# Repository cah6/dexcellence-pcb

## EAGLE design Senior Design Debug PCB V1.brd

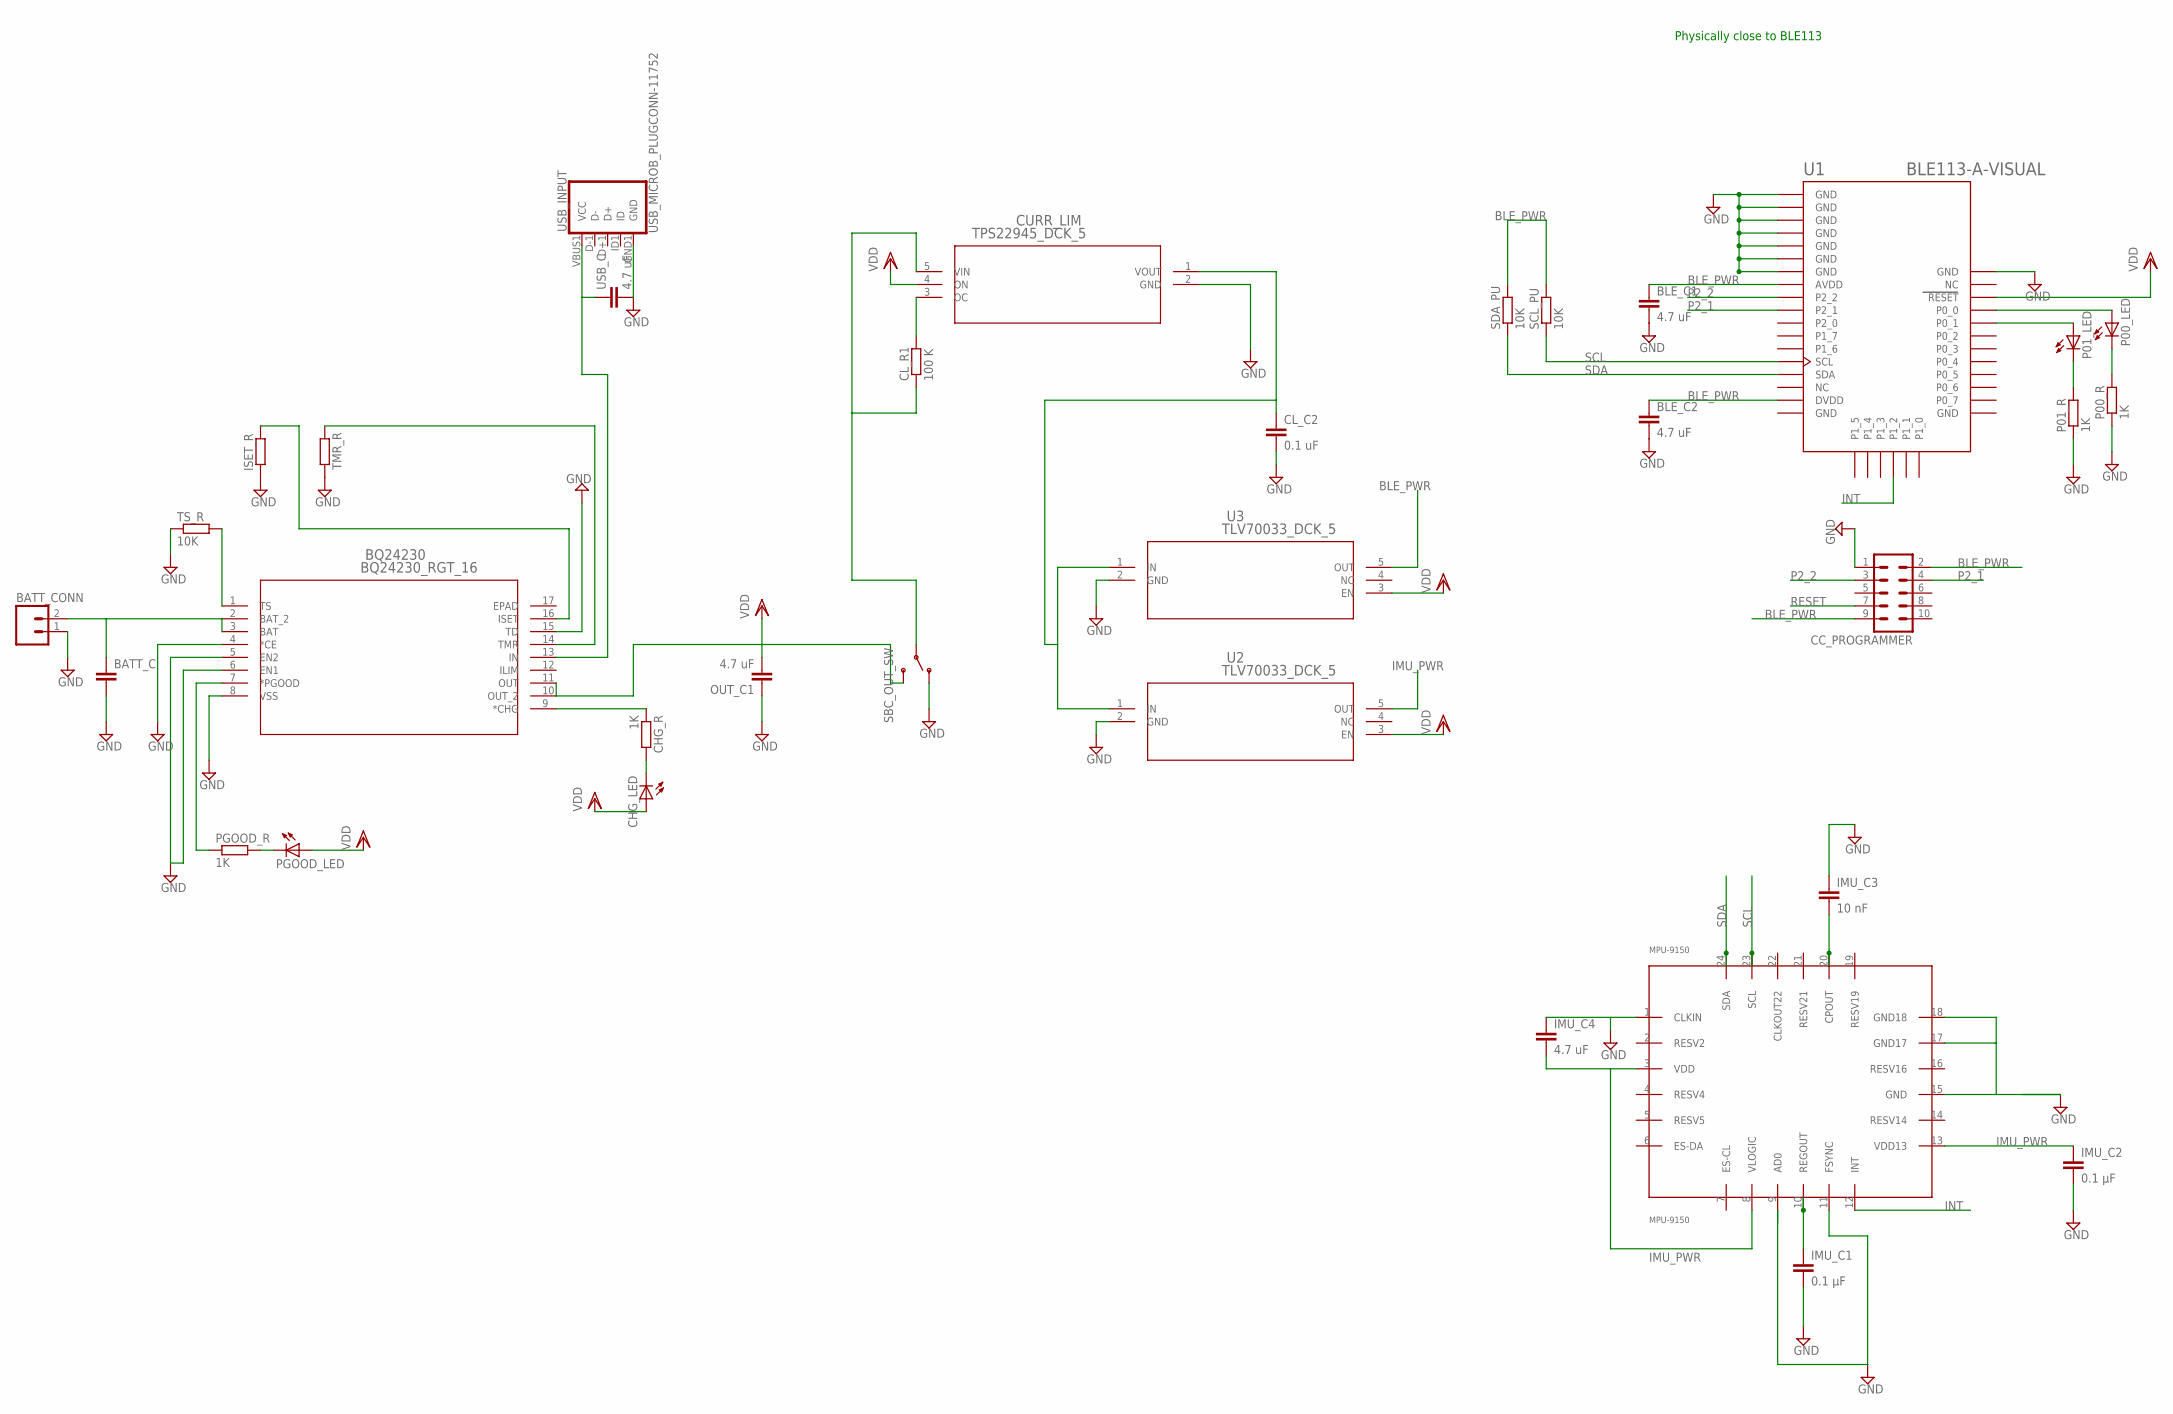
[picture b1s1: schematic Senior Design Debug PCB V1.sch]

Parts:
BATT_C: C; C0805
BATT_CONN: M02; 02P
BLE_C1, BLE_C2: 4.7 uF; C0805
BQ24230: BQ24230_RGT_16; RGT16_1P7X1P7
CC_PROGRAMMER: MA05-2
CHG_LED: LED_E; LED_1206
CHG_R: 1K; R0805
CL_C2: 0.1 uF; C0805
CL_R1: 100 K; R0805
CURR_LIM: TPS22945_DCK_5; DCK5
IMU_C1, IMU_C2: 0.1 µF; C0805
IMU_C3: 10 nF; C0805
IMU_C4: 4.7 uF; C0805
ISET_R: R; R0805
MPU-9150: MPU-9150
OUT_C1: 4.7 uF; C0805
P00_LED, P01_LED: LED_E; LED_1206
P00_R, P01_R: 1K; R0805
PGOOD_LED: LED_E; LED_1206
PGOOD_R: 1K; R0805
SBC_OUT_SW: SWITCH-SPDTPTH; SWITCH-SPDT
SCL_PU: 10K; R0805
SDA_PU: 10K; R0805
TMR_R: R; R0805
TS_R: 10K; R0805
U1: BLE113-A-VISUAL; BLE113-A
U2, U3: TLV70033_DCK_5; DCK5
USB_C: 4.7 uF; C0805
USB_INPUT: USB_MICROB_PLUGCONN-11752; USB-B-MICRO-SMD_V03

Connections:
BLE_PWR: BLE_C1.1, BLE_C2.1, CC_PROGRAMMER.2, CC_PROGRAMMER.9, SCL_PU.2, SDA_PU.2, U1.AVDD, U1.DVDD, U3.5 (OUT)
DC_IN: BQ24230.13 (IN), USB_C.1, USB_INPUT.VBUS1 (VCC)
EPAD: BQ24230.17 (EPAD)
GND: BATT_C.2, BATT_CONN.1, BLE_C1.2, BLE_C2.2, BQ24230.4 (*CE), BQ24230.5 (EN2), BQ24230.6 (EN1), BQ24230.8 (VSS), BQ24230.15 (TD), CC_PROGRAMMER.1, CL_C2.2, CURR_LIM.2 (GND), IMU_C1.2, IMU_C2.2, IMU_C3.1, IMU_C4.1, ISET_R.1, MPU-9150.1 (CLKIN), MPU-9150.9 (AD0), MPU-9150.11 (FSYNC), MPU-9150.15 (GND), MPU-9150.17 (GND17), MPU-9150.18 (GND18), OUT_C1.1, P00_R.1, P01_R.1, SBC_OUT_SW.1 (O), TMR_R.2, TS_R.1, U1.GND, U1.GND@2 (GND), U1.GND@3 (GND), U1.GND@4 (GND), U1.GND@5 (GND), U1.GND@6 (GND), U1.GND@7 (GND), U1.GND@8 (GND), U1.GND@9 (GND), U1.GND@10 (GND), U2.2 (GND), U3.2 (GND), USB_C.2, USB_INPUT.GND1 (GND)
IMU_PWR: IMU_C2.1, IMU_C4.2, MPU-9150.3 (VDD), MPU-9150.8 (VLOGIC), MPU-9150.13 (VDD13), U2.5 (OUT)
INT: MPU-9150.12 (INT), U1.P1_2
unnamed: IMU_C3.2, MPU-9150.20 (CPOUT)
unnamed: BQ24230.16 (ISET), ISET_R.2
unnamed: IMU_C1.1, MPU-9150.10 (REGOUT)
unnamed: CHG_LED.C, CHG_R.2
unnamed: BQ24230.9 (*CHG), CHG_R.1
unnamed: PGOOD_LED.C, PGOOD_R.2
unnamed: P00_LED.A, U1.P0_0
unnamed: CL_C2.1, CURR_LIM.1 (VOUT), U2.1 (IN), U3.1 (IN)
unnamed: P01_LED.A, U1.P0_1
unnamed: P01_LED.C, P01_R.2
unnamed: P00_LED.C, P00_R.2
unnamed: CL_R1.2, CURR_LIM.3 (OC)
unnamed: BQ24230.1 (TS), TS_R.2
unnamed: BATT_C.1, BATT_CONN.2, BQ24230.2 (BAT_2), BQ24230.3 (BAT)
unnamed: BQ24230.7 (*PGOOD), PGOOD_R.1
unnamed: CL_R1.1, CURR_LIM.5 (VIN), SBC_OUT_SW.2
unnamed: BQ24230.14 (TMR), TMR_R.1
P2_1: CC_PROGRAMMER.4, U1.P2_1
P2_2: CC_PROGRAMMER.3, U1.P2_2
RESET: CC_PROGRAMMER.7
SCL: MPU-9150.23 (SCL), SCL_PU.1, U1.SCL
SDA: MPU-9150.24 (SDA), SDA_PU.1, U1.SDA
VDD: BQ24230.10 (OUT_2), BQ24230.11 (OUT), CHG_LED.A, CURR_LIM.4 (ON), OUT_C1.2, PGOOD_LED.A, SBC_OUT_SW.3 (S), U1.RESET, U2.3 (EN), U3.3 (EN)

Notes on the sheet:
Physically close to BLE113

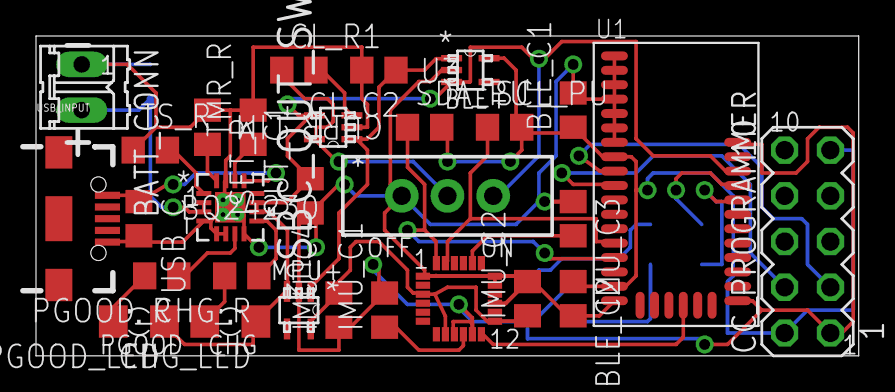
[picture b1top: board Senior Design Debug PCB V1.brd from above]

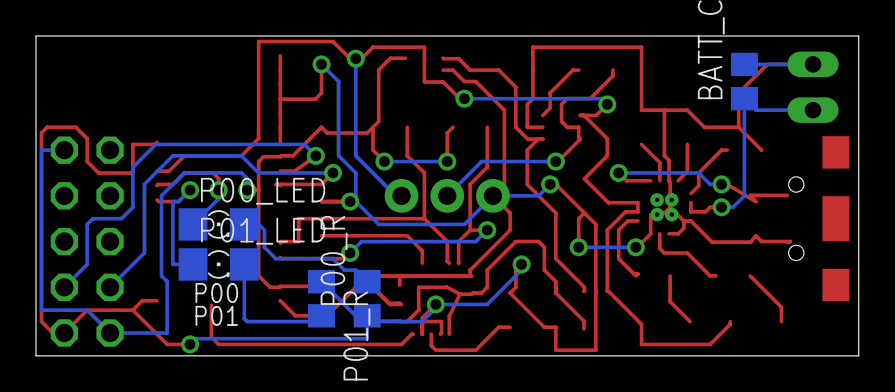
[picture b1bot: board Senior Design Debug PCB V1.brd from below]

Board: 2 copper layers, 45.7 x 17.8 mm, 34 parts (5 on the bottom side), 27 nets.

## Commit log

2014-03-07 initial commit, before revision 2 changes
2014-03-17 general layout for PCB, no traces yet
2014-03-17 parts laid out, ready to route
2014-03-17 finished almost all routing
2014-03-17 finished routing and silkscreen
2014-03-17 generated gerber files, deleted temp files
2014-03-17 changed a trace, remade gerber files

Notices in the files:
parts and their libraries:
SparkFun-Electromechanical: Licensing: CC v3.0 Share-Alike You are welcome to use this library for commercial purposes.
SparkFun-Connectors: Licensing: Creative Commons ShareAlike 4.0 International - https://creativecommons.org/licenses/by-sa/4.0
